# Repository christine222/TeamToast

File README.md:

# TeamToast
Micromouse 2017 - 2018

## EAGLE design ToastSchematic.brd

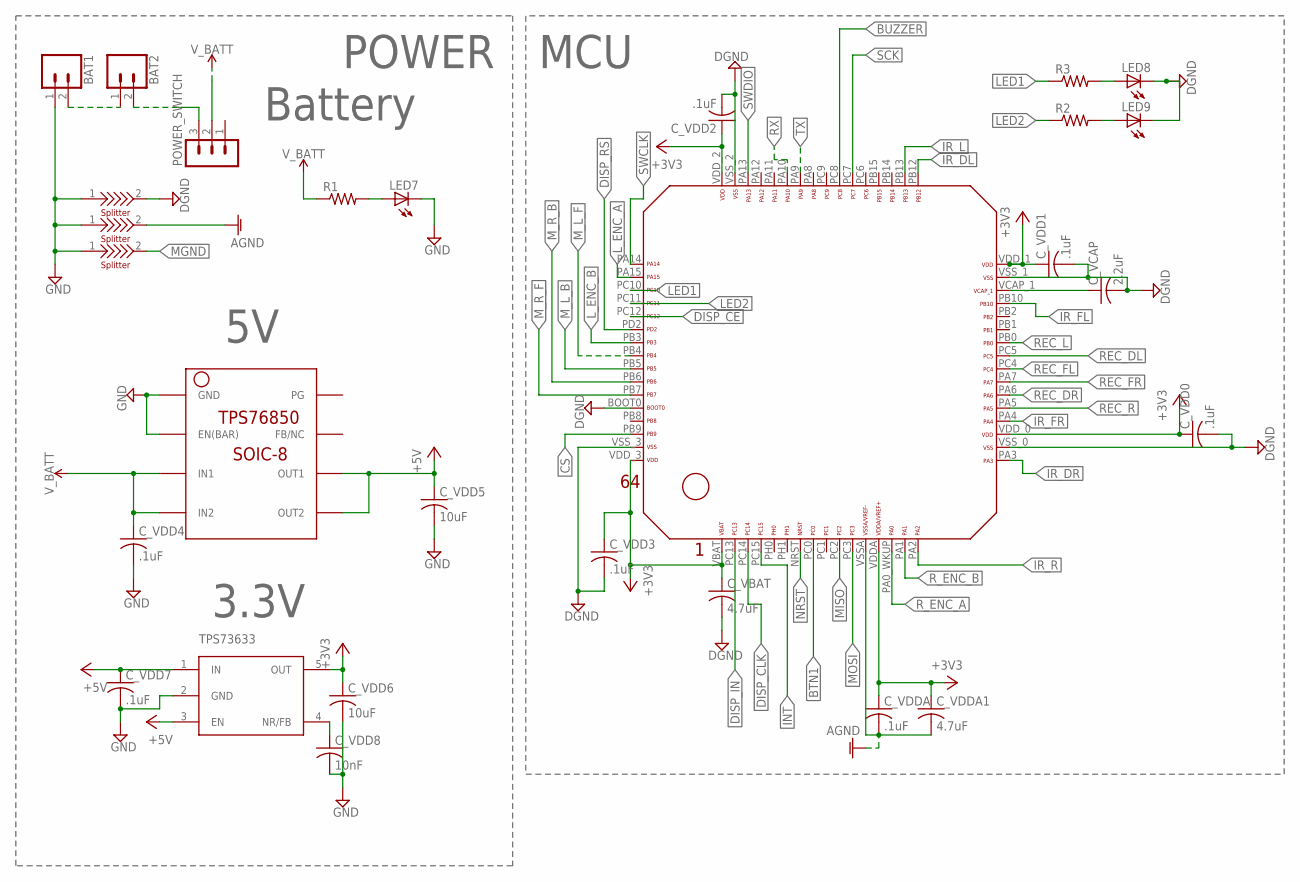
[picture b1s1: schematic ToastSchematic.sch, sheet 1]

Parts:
BAT1, BAT2: CONN_02JST-PTH-2; JST-2-PTH
C_VBAT: 4.7uF; C0603
C_VCAP: 2.2uF; C0603
C_VDD0, C_VDD1, C_VDD2, C_VDD3, C_VDD4, C_VDD7: .1uF; C0603
C_VDD5, C_VDD6: 10uF; C0603
C_VDD8: 10nF; C0603
C_VDDA: .1uF; C0603
C_VDDA1: 4.7uF; C0603
LED7: LED5MM
LED8, LED9: LEDCHIPLED_0603; CHIPLED_0603
POWER_SWITCH: MA03-1
R1, R2, R3: R-US_R0603; R0603
U$1: STM32F411/446_LQFP64
U$2: TPS73633; SOT23-5L
U$3: TPS76850(SOIC-8)
U$5, U$8, U$9: SPLITTER

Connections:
+3V3: C_VBAT.1, C_VDD0.1, C_VDD1.1, C_VDD2.1, C_VDD3.1, C_VDD6.1, C_VDDA.1, C_VDDA1.1, U$1.VBAT, U$1.VDDA, U$1.VDD_0, U$1.VDD_1, U$1.VDD_2, U$1.VDD_3, U$2.5 (OUT); also elsewhere on the board
+5V: C_VDD5.1, C_VDD7.1, U$2.1 (IN), U$2.3 (EN), U$3.OUT1, U$3.OUT2; also elsewhere on the board
AGND: C_VDDA.2, C_VDDA1.2, U$1.VSSA, U$8.2; also elsewhere on the board
BTN1: U$1.PC0; also elsewhere on the board
BUZZER: U$1.PC8; also elsewhere on the board
CS: U$1.PB9; also elsewhere on the board
DGND: C_VBAT.2, C_VCAP.2, C_VDD0.2, C_VDD1.2, C_VDD2.2, C_VDD3.2, LED8.C, LED9.C, U$1.BOOT0, U$1.VSS_0, U$1.VSS_1, U$1.VSS_2, U$1.VSS_3, U$5.2; also elsewhere on the board
DISP_CE: U$1.PC12; also elsewhere on the board
DISP_CLK: U$1.PC14; also elsewhere on the board
DISP_IN: U$1.PC13; also elsewhere on the board
DISP_RS: U$1.PD2; also elsewhere on the board
GND: BAT1.1, C_VDD4.2, C_VDD5.2, C_VDD6.2, C_VDD7.2, C_VDD8.2, LED7.K (C), U$2.2 (GND), U$3.EN(BAR), U$3.GND, U$5.1, U$8.1, U$9.1
INT: U$1.PC15; also elsewhere on the board
IR_DL: U$1.PB12; also elsewhere on the board
IR_DR: U$1.PA3; also elsewhere on the board
IR_FL: U$1.PB10; also elsewhere on the board
IR_FR: U$1.PA4; also elsewhere on the board
IR_L: U$1.PB13; also elsewhere on the board
IR_R: U$1.PA2; also elsewhere on the board
LED1: R3.1, U$1.PC10
LED2: R2.1, U$1.PC11
L_ENC_A: U$1.PA15; also elsewhere on the board
L_ENC_B: U$1.PB3; also elsewhere on the board
MGND: U$9.2; also elsewhere on the board
MISO: U$1.PC2; also elsewhere on the board
MOSI: U$1.PC3; also elsewhere on the board
M_L_B: U$1.PB5; also elsewhere on the board
M_L_F: U$1.PB4; also elsewhere on the board
M_R_B: U$1.PB6; also elsewhere on the board
M_R_F: U$1.PB7; also elsewhere on the board
unnamed: BAT1.2, BAT2.1
unnamed: BAT2.2, POWER_SWITCH.3
unnamed: C_VCAP.1, U$1.VCAP_1
unnamed: C_VDD8.1, U$2.4 (NR/FB)
unnamed: LED7.A, R1.2
unnamed: LED8.A, R3.2
unnamed: LED9.A, R2.2
NRST: U$1.NRST; also elsewhere on the board
REC_DL: U$1.PC5; also elsewhere on the board
REC_DR: U$1.PA6; also elsewhere on the board
REC_FL: U$1.PC4; also elsewhere on the board
REC_FR: U$1.PA7; also elsewhere on the board
REC_L: U$1.PB0; also elsewhere on the board
REC_R: U$1.PA5; also elsewhere on the board
RX: U$1.PA10; also elsewhere on the board
R_ENC_A: U$1.PA0_WKUP (PA0_AKUP); also elsewhere on the board
R_ENC_B: U$1.PA1; also elsewhere on the board
SCK: U$1.PC7; also elsewhere on the board
SWCLK: U$1.PA14; also elsewhere on the board
SWDIO: U$1.PA13; also elsewhere on the board
TX: U$1.PA9; also elsewhere on the board
V_BATT: C_VDD4.1, POWER_SWITCH.2, R1.1, U$3.IN1, U$3.IN2; also elsewhere on the board

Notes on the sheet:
MCU
POWER
3.3V
Battery

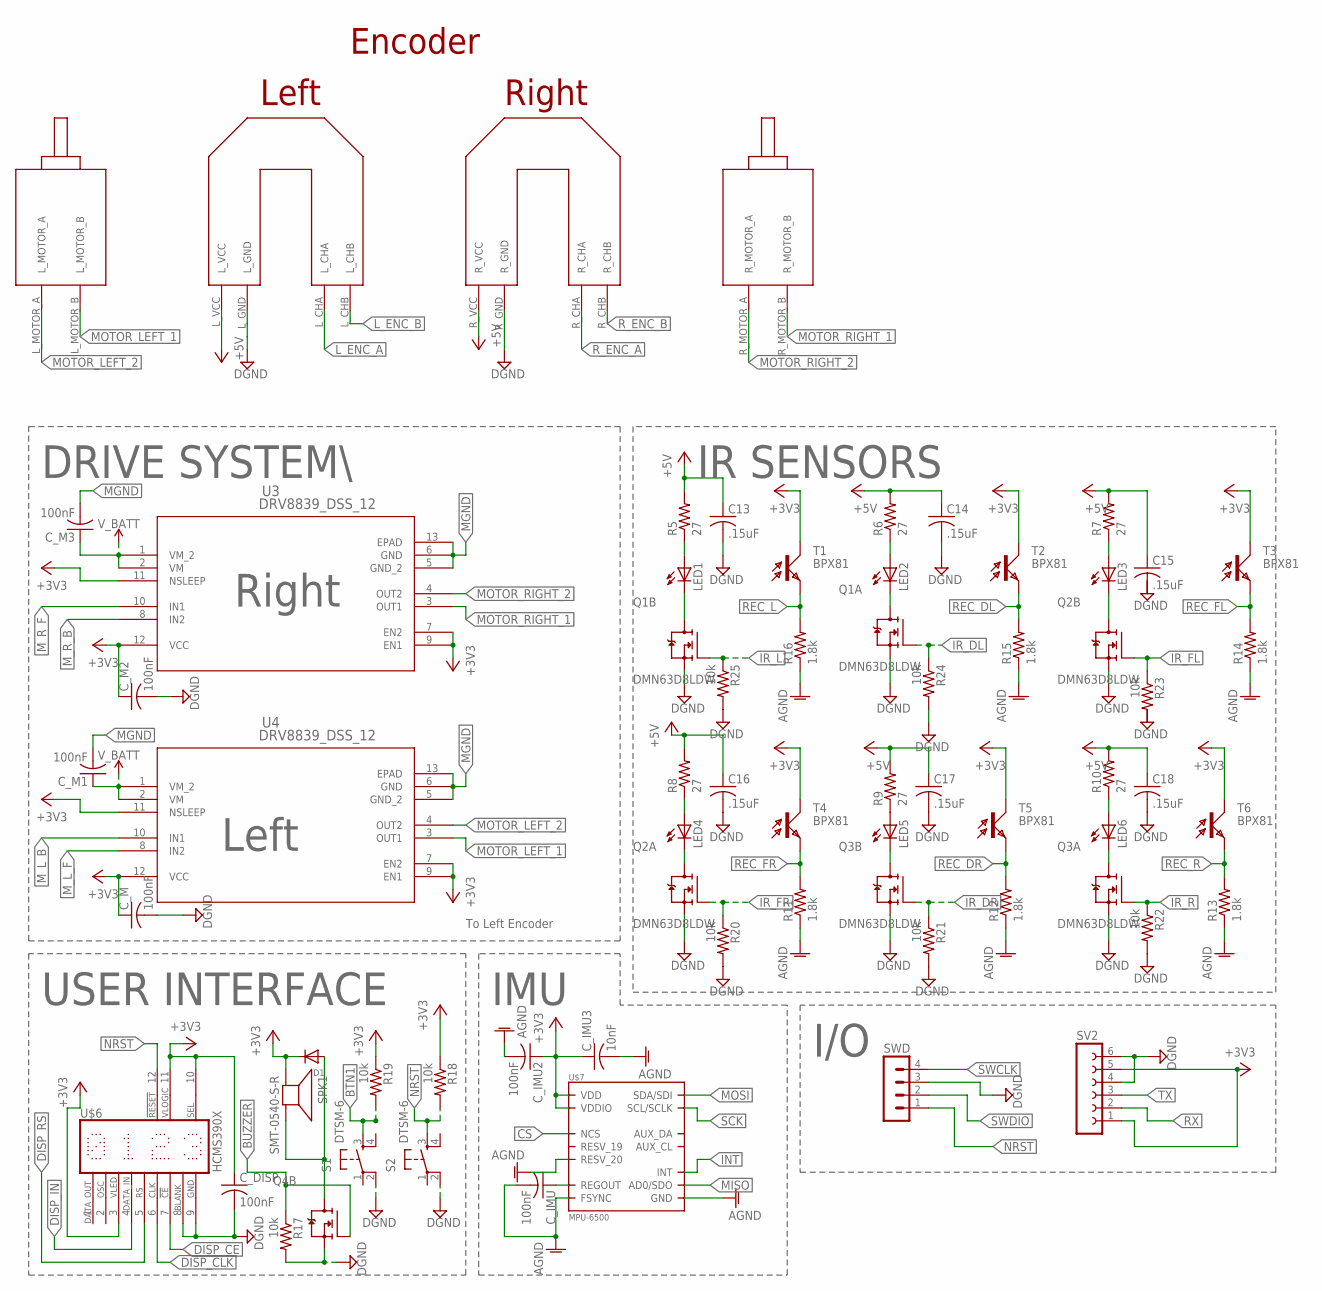
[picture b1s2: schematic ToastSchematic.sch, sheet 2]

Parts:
C13, C14, C15, C16, C17, C18: .15uF; C0603K
C_DISP: 100nF; C0603K
C_IMU, C_IMU2: 100nF; C0603K
C_IMU3: 10nF; C0603K
C_M, C_M1, C_M2, C_M3: 100nF; C0603K
D1: DIODESOD-323F; SOD-323F
LED1, LED2, LED3, LED4, LED5, LED6: LED5MM
Q1, Q2, Q3, Q4: DMN63D8LDW; SOT363
R5, R6, R7, R8, R9, R10: 27; R0603
R11, R12, R13, R14, R15, R16: 1.8k; R0603
R17, R18, R19, R20, R21, R22, R23, R24, R25: 10k; R0603
S1, S2: DTSM-6
SPK1: SMT-0540-S-R
SV2: FE06-1; FE06
SWD: MA04-1
T1, T2, T3, T4, T5, T6: BPX81
U3, U4: DRV8839_DSS_12; DSS12_P9X2
U$4: FUTURA_V1.0_MOTOR_MOUNT; FUTURA_V1.0_MOTOT_MOUNT
U$6: HCMS390X
U$7: MPU-6500; QFN.24.4X4

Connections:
+3V3: C_DISP.1, C_IMU2.1, C_IMU3.1, C_M.1, C_M2.1, D1.C, R18.1, R19.1, SPK1.- (+), SV2.1, SV2.5, T1.C, T2.C, T3.C, T4.C, T5.C, T6.C, U3.7 (EN2), U3.9 (EN1), U3.11 (NSLEEP), U3.12 (VCC), U4.7 (EN2), U4.9 (EN1), U4.11 (NSLEEP), U4.12 (VCC), U$6.3 (VLED), U$6.10 (SEL), U$6.11 (VLOGIC), U$7.8 (VDDIO), U$7.13 (VDD); also elsewhere on the board
+5V: C13.1, C14.1, C15.1, C16.1, C17.1, C18.1, R5.2, R6.2, R7.2, R8.2, R9.2, R10.2, U$4.L_VCC, U$4.R_VCC; also elsewhere on the board
AGND: C_IMU.2, C_IMU2.2, C_IMU3.2, R11.1, R12.1, R13.1, R14.1, R15.1, R16.1, U$7.11 (FSYNC), U$7.18 (GND), U$7.20 (RESV_20); also elsewhere on the board
BTN1: R19.2, S1.3; also elsewhere on the board
BUZZER: Q4.5 (G), R17.1; also elsewhere on the board
CS: U$7.22 (NCS); also elsewhere on the board
DGND: C13.2, C14.2, C16.2, C17.2, C18.2, C_DISP.2, C_M.2, C_M2.2, Q1.1 (S), Q1.4 (S), Q2.1 (S), Q2.4 (S), Q3.1 (S), Q3.4 (S), Q4.4 (S), R17.2, R20.2, R21.2, R22.2, R24.2, R25.2, S1.2, S2.2, SV2.4, SV2.6, SWD.3, U$4.L_GND, U$4.R_GND, U$6.8 (BLANK), U$6.9 (GND); also elsewhere on the board
DISP_CE: U$6.7 (!CE); also elsewhere on the board
DISP_CLK: U$6.6 (CLK); also elsewhere on the board
DISP_IN: U$6.4 (IN); also elsewhere on the board
DISP_RS: U$6.5 (RS); also elsewhere on the board
INT: U$7.12 (INT); also elsewhere on the board
IR_DL: Q1.2 (G), R24.1; also elsewhere on the board
IR_DR: Q3.5 (G), R21.1; also elsewhere on the board
IR_FL: Q2.5 (G), R23.1; also elsewhere on the board
IR_FR: Q2.2 (G), R20.1; also elsewhere on the board
IR_L: Q1.5 (G), R25.1; also elsewhere on the board
IR_R: Q3.2 (G), R22.1; also elsewhere on the board
L_ENC_A: U$4.L_CHA; also elsewhere on the board
L_ENC_B: U$4.L_CHB; also elsewhere on the board
MGND: C_M1.2, C_M3.2, U3.5 (GND_2), U3.6 (GND), U3.13 (EPAD), U4.5 (GND_2), U4.6 (GND), U4.13 (EPAD); also elsewhere on the board
MISO: U$7.9 (AD0/SDO); also elsewhere on the board
MOSI: U$7.24 (SDA/SDI); also elsewhere on the board
MOTOR_LEFT_1: U4.3 (OUT1), U$4.L_MOTOR_B
MOTOR_LEFT_2: U4.4 (OUT2), U$4.L_MOTOR_A
MOTOR_RIGHT_1: U3.3 (OUT1), U$4.R_MOTOR_B
MOTOR_RIGHT_2: U3.4 (OUT2), U$4.R_MOTOR_A
M_L_B: U4.10 (IN1); also elsewhere on the board
M_L_F: U4.8 (IN2); also elsewhere on the board
M_R_B: U3.8 (IN2); also elsewhere on the board
M_R_F: U3.10 (IN1); also elsewhere on the board
unnamed: LED1.A, R5.1
unnamed: LED1.K (C), Q1.3 (D)
unnamed: LED2.A, R6.1
unnamed: LED2.K (C), Q1.6 (D)
unnamed: LED3.K (C), Q2.3 (D)
unnamed: LED3.A, R7.1
unnamed: LED6.A, R10.1
unnamed: LED6.K (C), Q3.6 (D)
unnamed: LED4.A, R8.1
unnamed: C_IMU.1, U$7.10 (REGOUT)
unnamed: LED4.K (C), Q2.6 (D)
unnamed: LED5.A, R9.1
unnamed: LED5.K (C), Q3.3 (D)
unnamed: D1.A, Q4.3 (D), SPK1.+ (-)
NRST: R18.2, S2.3, SWD.1, U$6.12 (NOT_RESET); also elsewhere on the board
REC_DL: R15.2, T2.E; also elsewhere on the board
REC_DR: R12.2, T5.E; also elsewhere on the board
REC_FL: R14.2, T3.E; also elsewhere on the board
REC_FR: R11.2, T4.E; also elsewhere on the board
REC_L: R16.2, T1.E; also elsewhere on the board
REC_R: R13.2, T6.E; also elsewhere on the board
RX: SV2.2; also elsewhere on the board
R_ENC_A: U$4.R_CHA; also elsewhere on the board
R_ENC_B: U$4.R_CHB; also elsewhere on the board
SCK: U$7.23 (SCL/SCLK); also elsewhere on the board
SWCLK: SWD.4; also elsewhere on the board
SWDIO: SWD.2; also elsewhere on the board
TX: SV2.3; also elsewhere on the board
V_BATT: C_M1.1, C_M3.1, U3.1 (VM_2), U3.2 (VM), U4.1 (VM_2), U4.2 (VM); also elsewhere on the board

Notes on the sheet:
DRIVE SYSTEM\
Right
Left
USER INTERFACE
IR SENSORS
IMU
I/O
To Left Encoder

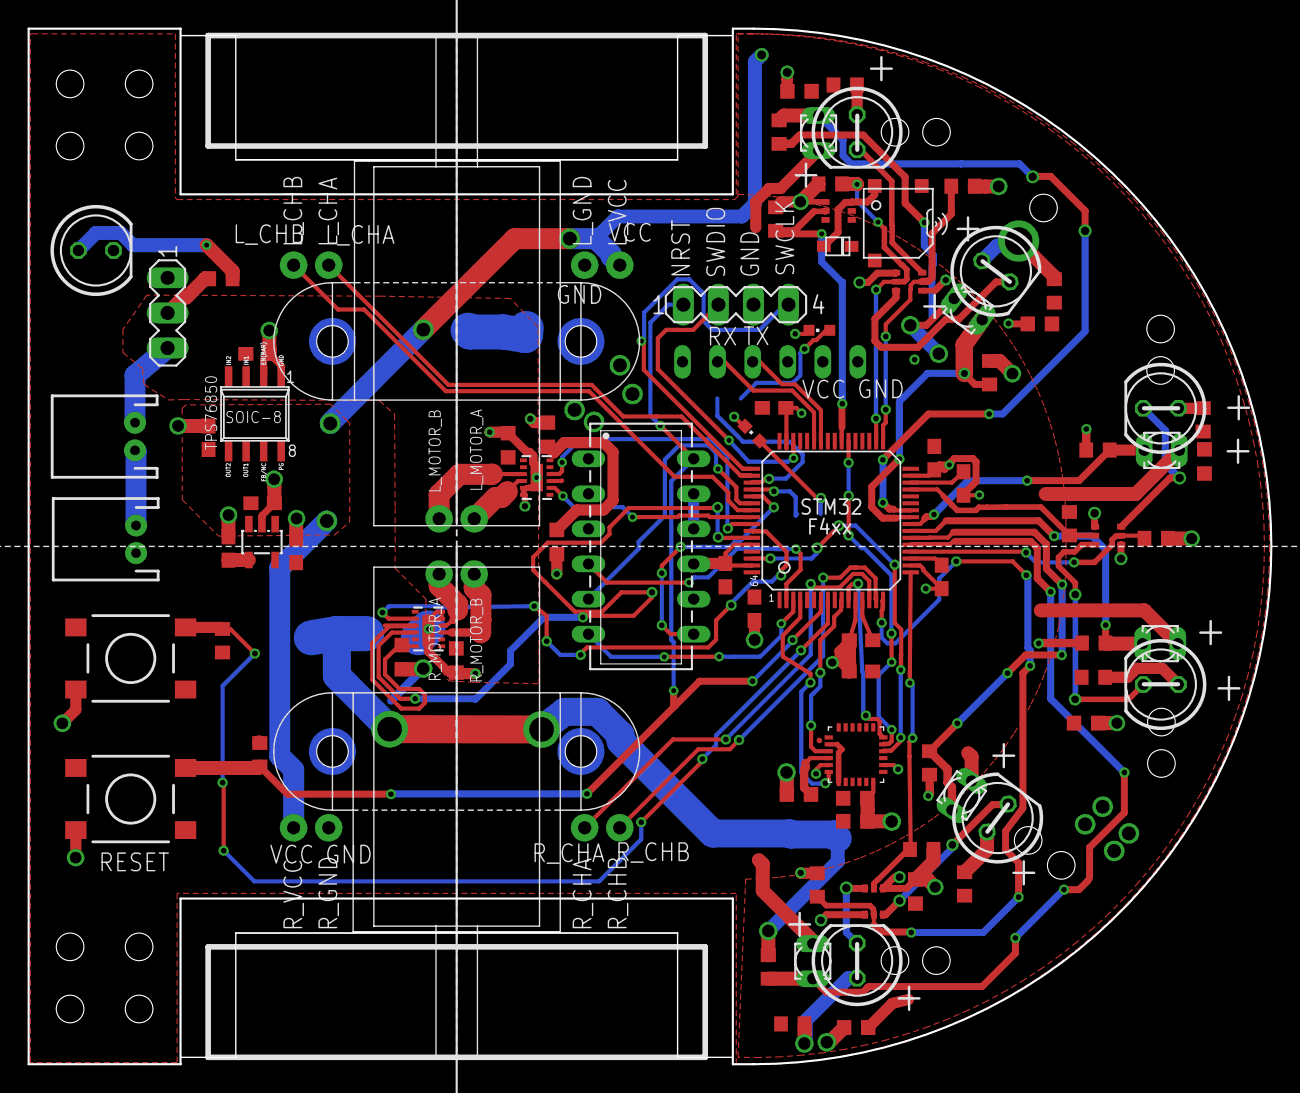
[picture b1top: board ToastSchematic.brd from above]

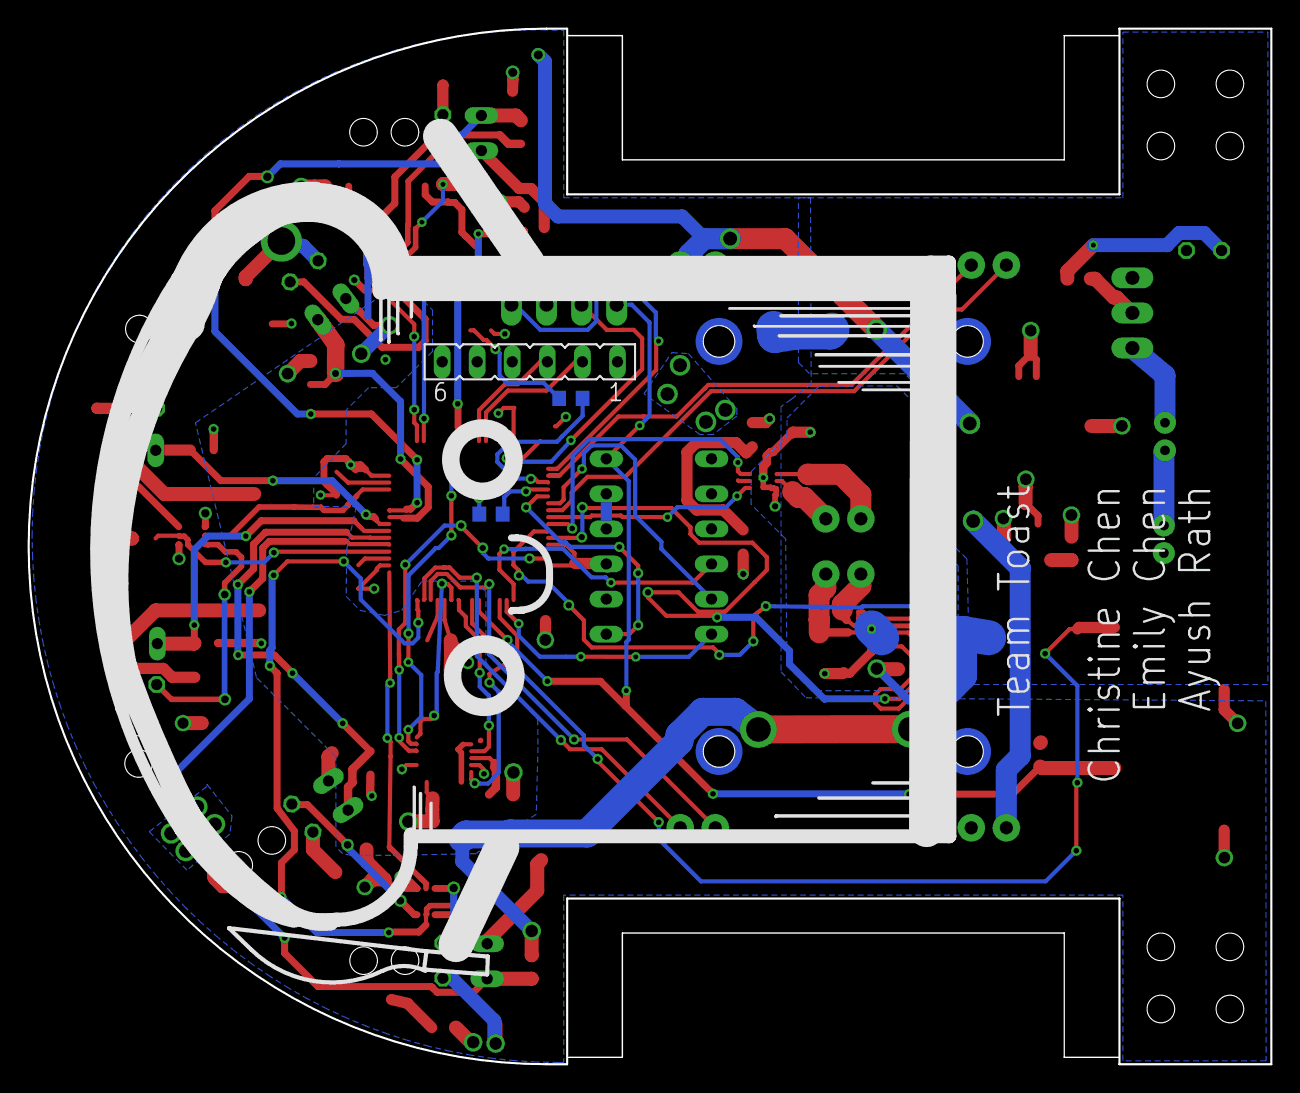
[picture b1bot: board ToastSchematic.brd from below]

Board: 2 copper layers, 90.0 x 75.0 mm, 90 parts (6 on the bottom side), 70 nets.

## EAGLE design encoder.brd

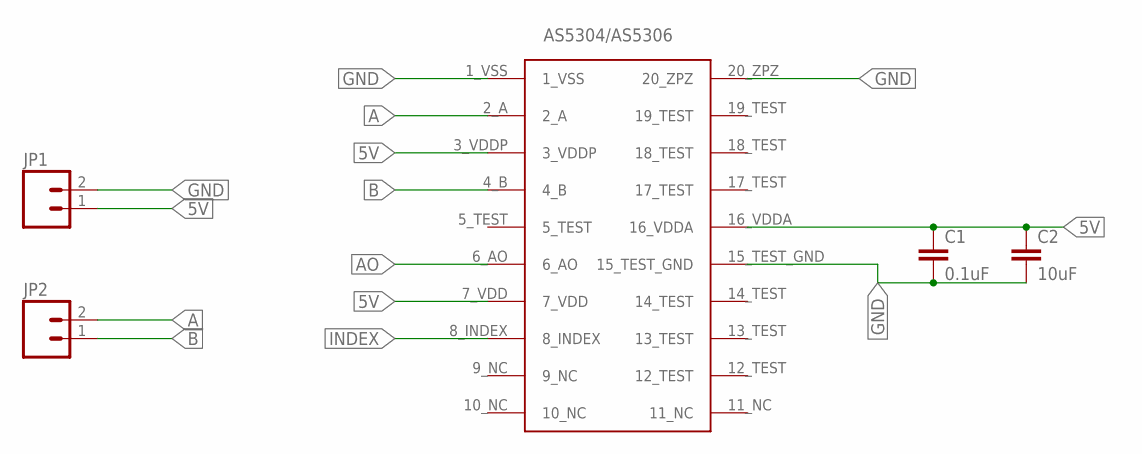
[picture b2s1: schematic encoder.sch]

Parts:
C1: 0.1uF; C0603
C2: 10uF; C0603
JP1, JP2: M02LOCK; 1X02_LOCK
U$1: AS5304/AS5306-ENCODER

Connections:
5V: C1.1, C2.1, JP1.1, U$1.3_VDDP, U$1.7_VDD, U$1.16_VDDA
A: JP2.2, U$1.2_A
AO: U$1.6_AO
B: JP2.1, U$1.4_B
GND: C1.2, C2.2, JP1.2, U$1.1_VSS, U$1.15_TEST_GND, U$1.20_ZPZ
INDEX: U$1.8_INDEX

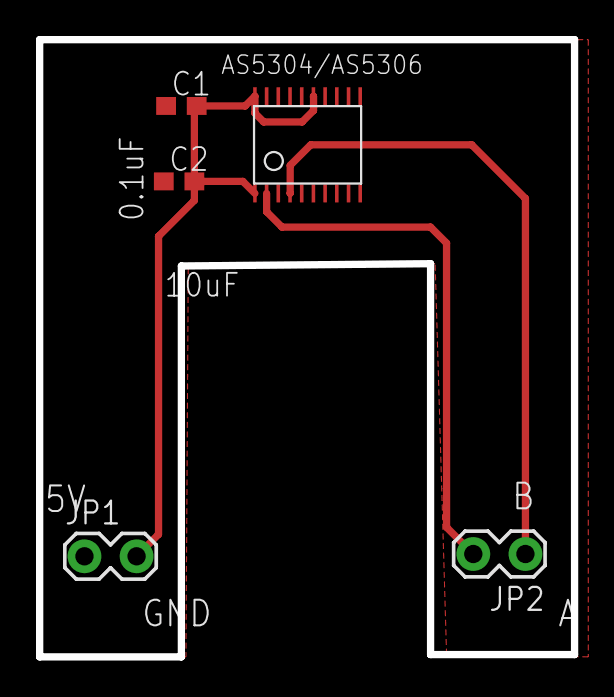
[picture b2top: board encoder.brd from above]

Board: 2 copper layers, 29.7 x 34.3 mm, 5 parts (0 on the bottom side), 4 nets.

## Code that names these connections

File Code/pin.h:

#ifndef PIN_H
#define PIN_H

#include "mbed.h"

//IR LEDs
#define IR_R_PIN PA_2
#define IR_DR_PIN PA_3
#define IR_FR_PIN PA_4
#define IR_FL_PIN PB_10
#define IR_DL_PIN PB_12
#define IR_L_PIN PB_13

//Phototransistors
#define PT_R_PIN PA_5
#define PT_DR_PIN PA_6
#define PT_FR_PIN PA_7
#define PT_FL_PIN PC_4
#define PT_DL_PIN PC_5
#define PT_L_PIN PB_0

//Motors
#define MTR_R_FWD_PIN PB_6
#define MTR_R_REV_PIN PB_7
#define MTR_L_FWD_PIN PB_4
#define MTR_L_REV_PIN PB_5

//Encoders
#define L_ENC_A_PIN PA_15
#define L_ENC_B_PIN PB_3
#define R_ENC_A_PIN PA_0
#define R_ENC_B_PIN PA_1

//User I/O
#define LED_1_PIN PC_10
#define LED_2_PIN PC_11
#define BTN_1_PIN PC_0
#define RX_PIN PA_10
#define TX_PIN PA_9
/*
Display Stuff
*/
#define DISP_CE_PIN PC_12
#define DISP_IN_PIN PC_13
#define DISP_CLK_PIN PC_14

#endif

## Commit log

2017-11-08 Added schematic to repo
2017-11-08 Adding Futura Encoders
    encoder brd and sch
2017-11-09 started pcb board layout
    put parts where they should be
2017-11-09 added gnd plane
    added gnd plane
2017-11-09 did dgnd, agnd, and gnd planes
    added some traces, still need to add all the power planes
2017-11-09 added 5V plane
2017-11-10 some routing
    Partially routed IRs and other stuff
2017-11-10 Restarted routing
2017-11-10 Added Ground Splitter
2017-11-10 Get everything on cheap week
2017-11-11 Did more routing
2017-11-25 Finished Routing Board
2017-11-27 Added text to bottom of board
2017-11-30 Minor Fixes
2017-11-30 added routing and some mounting holes
2017-12-01 fixed bottleneck and minor issues
2017-12-01 Added mounting holes for IR
2017-12-01 finished wiring everything
    still need to add toast and butter pics on the back and smash and label
    stuff
2017-12-01 Added art to board
2018-05-19 Added code
    Added first code files
2018-05-19 Removed unused folder

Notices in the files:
parts and their libraries:
SparkFun-Connectors: Licensing: Creative Commons ShareAlike 4.0 International - https://creativecommons.org/licenses/by-sa/4.0
SparkFun: Licensing: CC v3.0 Share-Alike You are welcome to use this library for commercial purposes.
